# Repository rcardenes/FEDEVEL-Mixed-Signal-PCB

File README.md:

Mixed-Signal Demo PCB
=====================

Demo board project for the "Mixed-Signal Hardware Design with KiCAD" course, by
Phil Salmony (of Phil's Lab fame) at [FEDEVEL](fedevel.com). 

The project was created from scratch using KiCAD 8.0, following the course lectures.
It comes with all the relevant files, including missing footprints and 3D models.
Several of the 3D models were downloaded, and are not to be used without permission:

- HRO_TYPE-C-31-M-12.step (USB receptacle, from GrabCad.com)
- 31-5640-1010.stp (BNC connectors, from Amphenol.com)
- L_Coilcraft_XxL4020.step (for the matching inductor, from 3DContentCentral.com)

The models for the CMF3216 common-mode choke, and the RGB LED (E6C...) were created
by myself in FreeCAD and are free to use, with appropriate acknowledgment.

The project includes Gerber files, and BOM/Placement files. All relevant parts include
an MNP field with JCLPCB/LCSC part numbers, and the assembly files were generated using
the "Fabrication Toolkit" plugin, which generates JLCPCB-compatible output.

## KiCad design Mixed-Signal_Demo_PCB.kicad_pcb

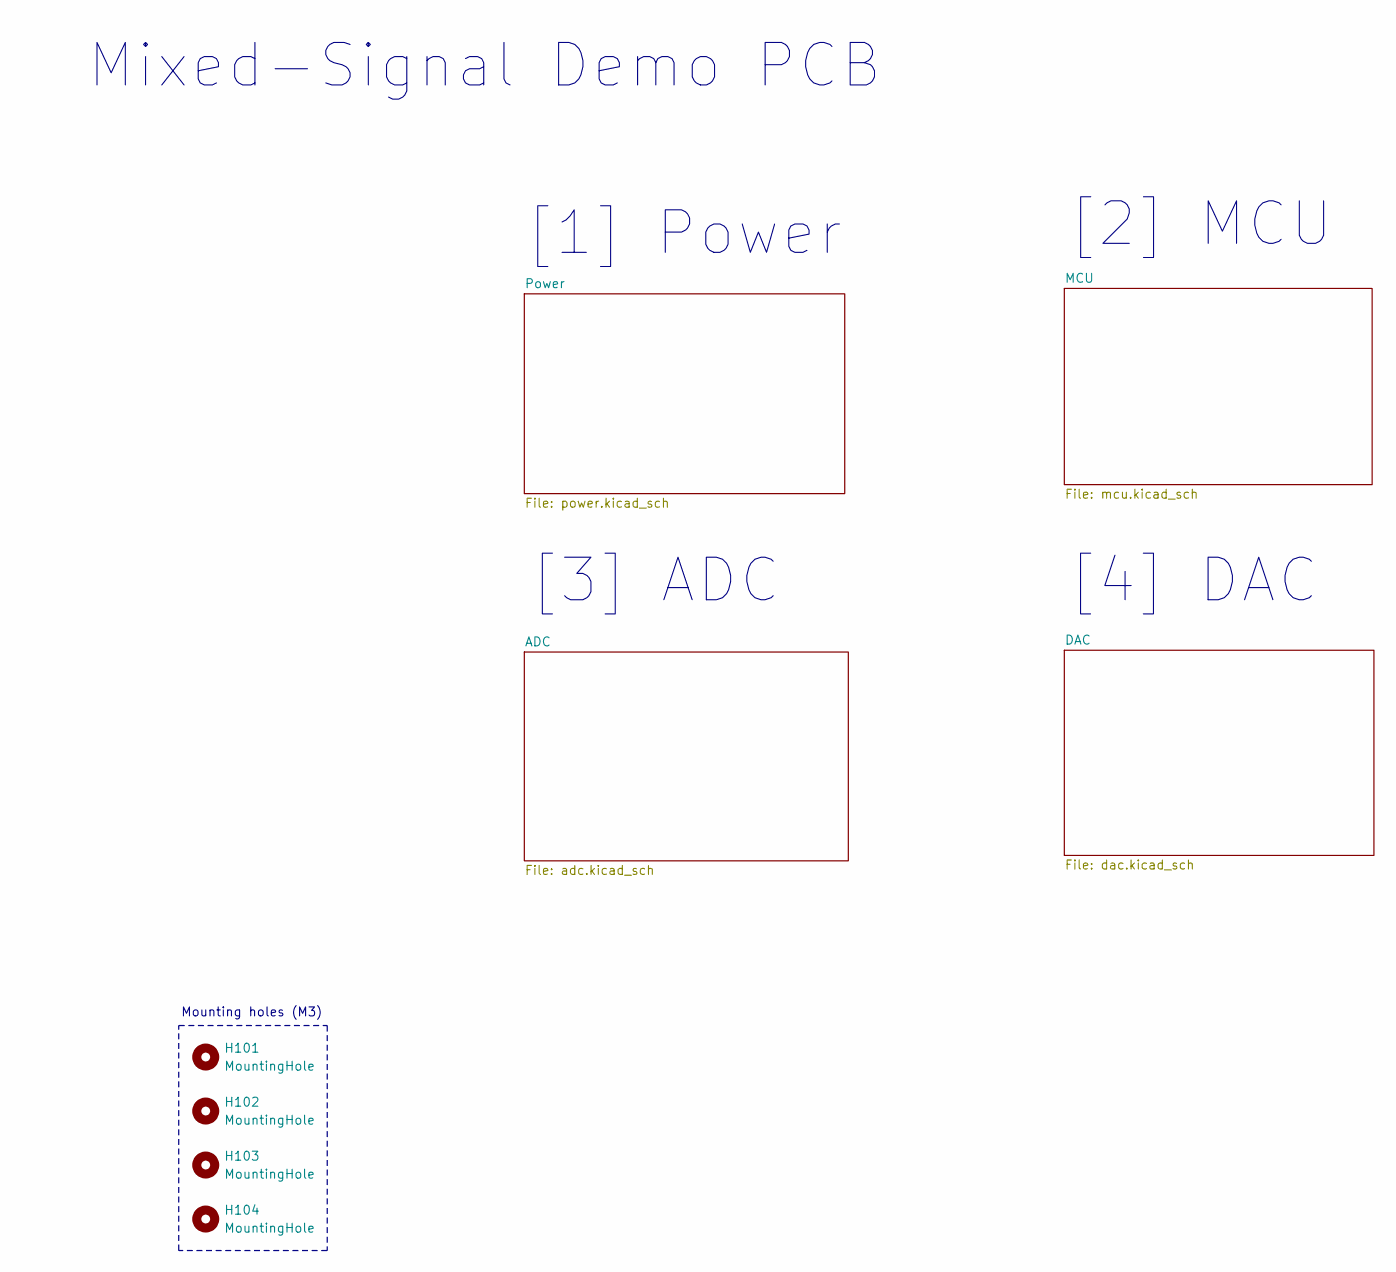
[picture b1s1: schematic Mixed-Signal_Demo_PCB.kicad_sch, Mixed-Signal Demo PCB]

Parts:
H101, H102, H103, H104: MountingHole; MountingHole_3.2mm_M3

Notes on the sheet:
[2] MCU
[1] Power
[3] ADC
[4] DAC
Mounting holes (M3)
Mixed-Signal Demo PCB

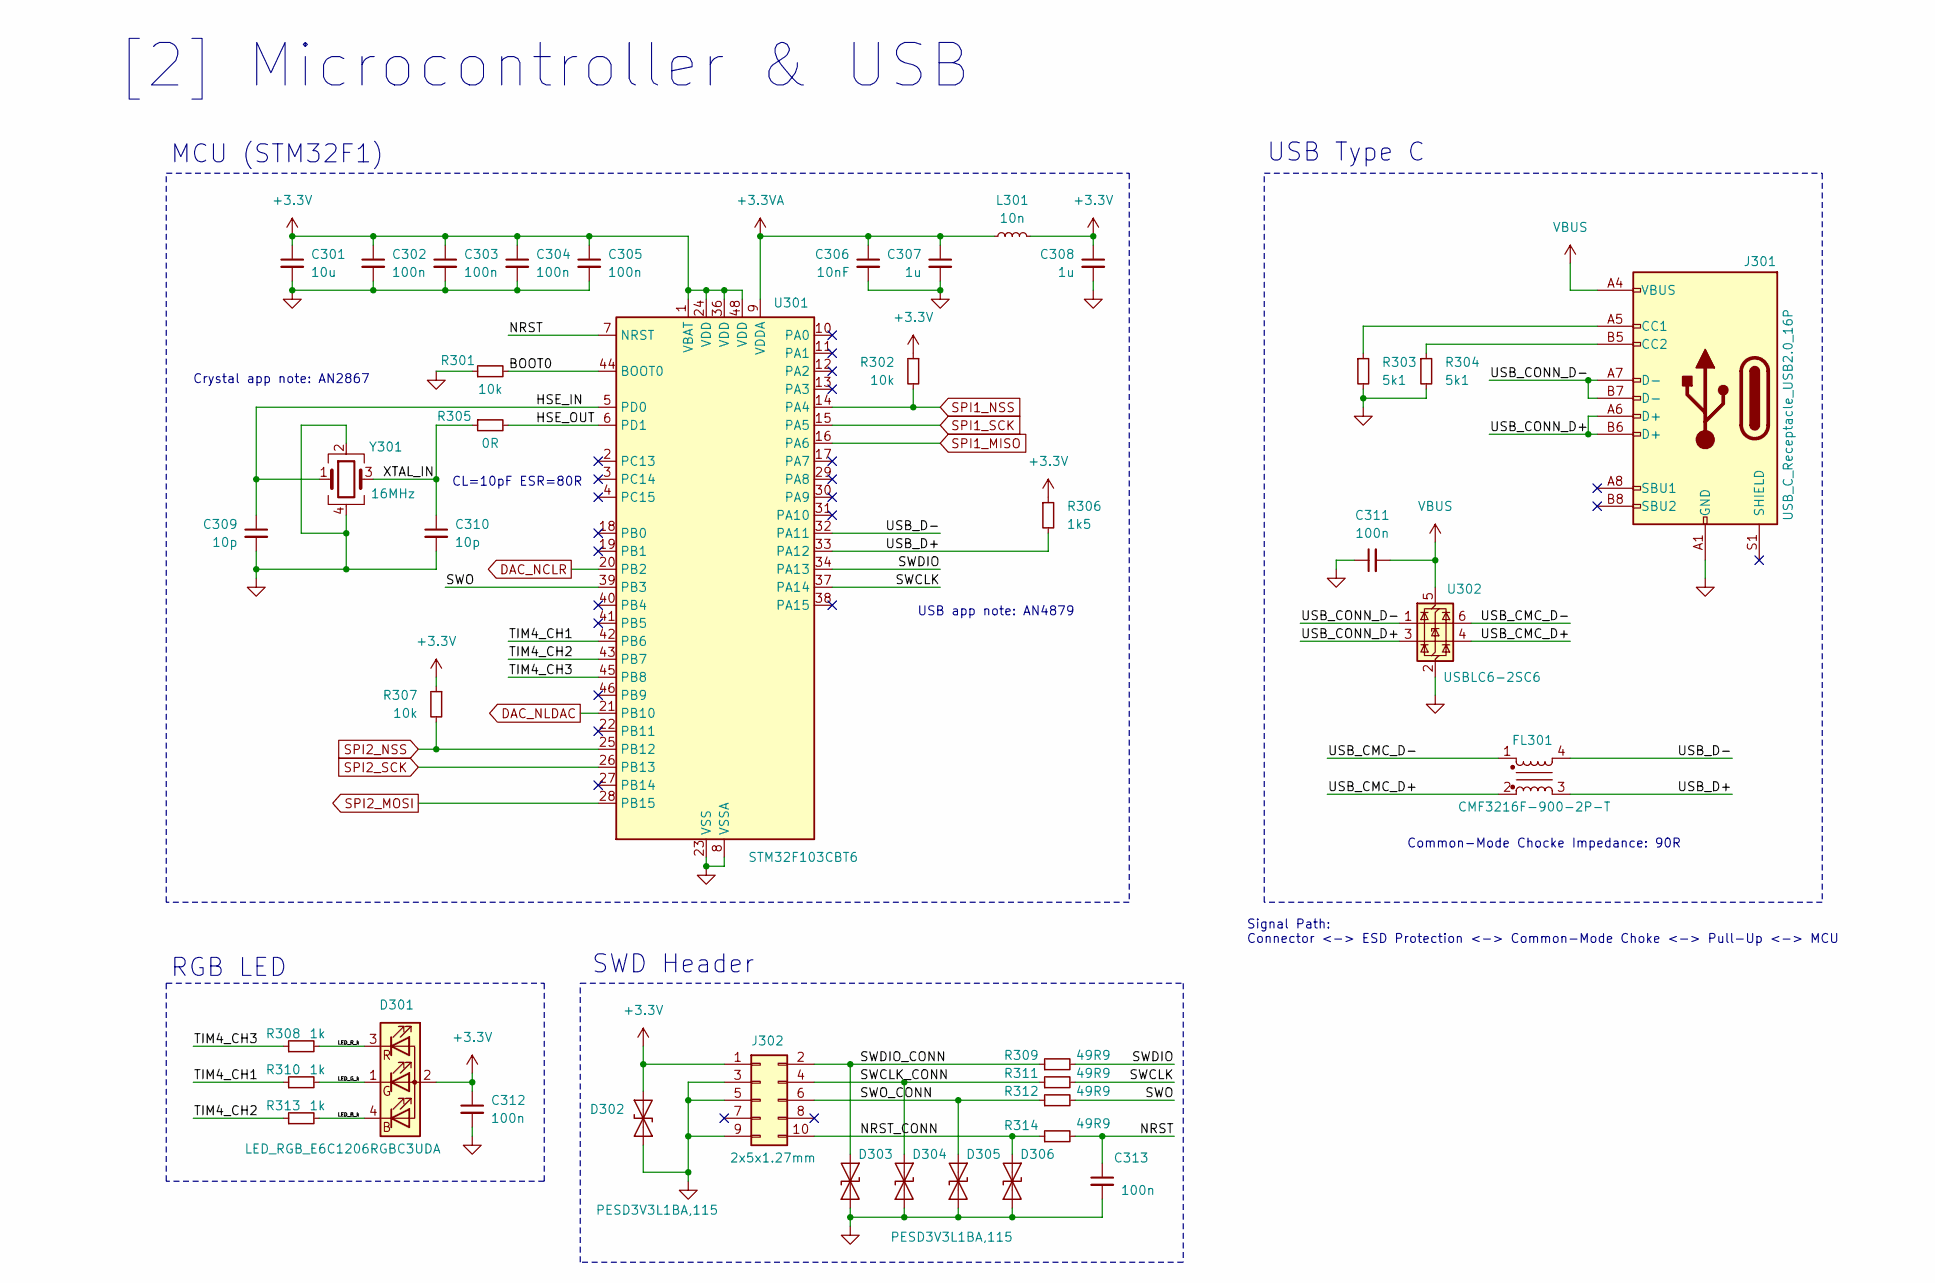
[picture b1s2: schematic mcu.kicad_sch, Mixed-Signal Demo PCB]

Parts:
C301: 10u; C_0603_1608Metric; MPN C19702
C302, C303, C304, C305, C311, C312, C313: 100n; C_0402_1005Metric; MPN C1525
C306: 10nF; C_0402_1005Metric; MPN C15195
C307, C308: 1u; C_0603_1608Metric; MPN C15849
C309, C310: 10p; C_0402_1005Metric; MPN C32949
D301: LED_RGB_E6C1206RGBC3UDA; E6C1206RGBC3UDA; MPN C375571
D302, D303, D304, D305, D306: PESD3V3L1BA,115; D_SOD-323; MPN C51450
FL301: CMF3216F-900-2P-T; CMF3216F; MPN C963740
J301: USB_C_Receptacle_USB2.0_16P; USB_C_Receptacle_HRO_TYPE-C-31-M-12; MPN C319148
J302: 2x5x1.27mm; PinHeader_2x05_P1.27mm_Vertical_SMD; MPN C920813
L301: 10n; L_0402_1005Metric; MPN C404632
R301, R302, R307: 10k; R_0402_1005Metric; MPN C25744
R303, R304: 5k1; R_0402_1005Metric; MPN C25905
R305: 0R; R_0402_1005Metric; MPN C17168
R306: 1k5; R_0402_1005Metric; MPN C25867
R308, R310, R313: 1k; R_0402_1005Metric; MPN C11702
R309, R311, R312, R314: 49R9; R_0402_1005Metric; MPN C25120
U301: STM32F103CBT6; LQFP-48_7x7mm_P0.5mm; MPN C8304
U302: USBLC6-2SC6; SOT-23-6; MPN USBLC6-2SC6
Y301: 16MHz; Crystal_SMD_3225-4Pin_3.2x2.5mm; MPN C362342

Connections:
+3.3V: C301.1, C302.1, C303.1, C304.1, C305.1, C308.1, C312.1, D301.2 (A), D302.2 (A2), J302.1, L301.2, R302.1, R306.1, R307.1, U301.1 (VBAT), U301.24 (VDD), U301.36 (VDD), U301.48 (VDD); also elsewhere on the board
+3.3VA: C306.1, C307.1, L301.1, U301.9 (VDDA); also elsewhere on the board
/MCU/BOOT0: R301.2, U301.44 (BOOT0)
/MCU/HSE_IN: C309.1, U301.5 (PD0), Y301.1
/MCU/HSE_OUT: R305.2, U301.6 (PD1)
/MCU/LED_B_k: D301.4 (BK), R313.2
/MCU/LED_G_k: D301.1 (GK), R310.2
/MCU/LED_R_k: D301.3 (RK), R308.2
/MCU/NRST: C313.1, R314.2, U301.7 (NRST)
/MCU/NRST_CONN: D306.2 (A2), J302.10, R314.1
/MCU/SWCLK: R311.2, U301.37 (PA14)
/MCU/SWCLK_CONN: D304.2 (A2), J302.4, R311.1
/MCU/SWDIO: R309.2, U301.34 (PA13)
/MCU/SWDIO_CONN: D303.2 (A2), J302.2, R309.1
/MCU/SWO: R312.2, U301.39 (PB3)
/MCU/SWO_CONN: D305.2 (A2), J302.6, R312.1
/MCU/TIM4_CH1: R310.1, U301.42 (PB6)
/MCU/TIM4_CH2: R313.1, U301.43 (PB7)
/MCU/TIM4_CH3: R308.1, U301.45 (PB8)
/MCU/USB_CMC_D+: FL301.2, U302.4 (I/O2)
/MCU/USB_CMC_D-: FL301.1, U302.6 (I/O1)
/MCU/USB_CONN_D+: J301.A6 (D+), J301.B6 (D+), U302.3 (I/O2)
/MCU/USB_CONN_D-: J301.A7 (D-), J301.B7 (D-), U302.1 (I/O1)
/MCU/USB_D+: FL301.3, R306.2, U301.33 (PA12)
/MCU/USB_D-: FL301.4, U301.32 (PA11)
/MCU/XTAL_IN: C310.1, R305.1, Y301.3
DAC_NCLR: U301.20 (PB2); also elsewhere on the board
DAC_NLDAC: U301.21 (PB10); also elsewhere on the board
GND: C301.2, C302.2, C303.2, C304.2, C305.2, C306.2, C307.2, C308.2, C309.2, C310.2, C311.1, C312.2, C313.2, D302.1 (A1), D303.1 (A1), D304.1 (A1), D305.1 (A1), D306.1 (A1), J301.A1 (GND), J301.A12 (GND), J301.B1 (GND), J301.B12 (GND), J302.3, J302.5, J302.9, R301.1, R303.2, R304.2, U301.8 (VSSA), U301.23 (VSS), U301.35 (VSS), U301.47 (VSS), U302.2 (GND), Y301.2, Y301.4; also elsewhere on the board
unnamed: J301.A5 (CC1), R303.1
unnamed: J301.B5 (CC2), R304.1
SPI1_MISO: U301.16 (PA6); also elsewhere on the board
SPI1_NSS: R302.2, U301.14 (PA4); also elsewhere on the board
SPI1_SCK: U301.15 (PA5); also elsewhere on the board
SPI2_MOSI: U301.28 (PB15); also elsewhere on the board
SPI2_NSS: R307.2, U301.25 (PB12); also elsewhere on the board
SPI2_SCK: U301.26 (PB13); also elsewhere on the board
VBUS: C311.2, J301.A4 (VBUS), J301.A9 (VBUS), J301.B4 (VBUS), J301.B9 (VBUS), U302.5 (VBUS); also elsewhere on the board

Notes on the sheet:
MCU (STM32F1)
[2] Microcontroller & USB
RGB LED
SWD Header
Crystal app note: AN2867
CL=10pF ESR=80R
Signal Path: Connector <-> ESD Protection <-> Common-Mode Choke <-> Pull-Up <-> MCU
USB app note: AN4879
Common-Mode Chocke Impedance: 90R
USB Type C

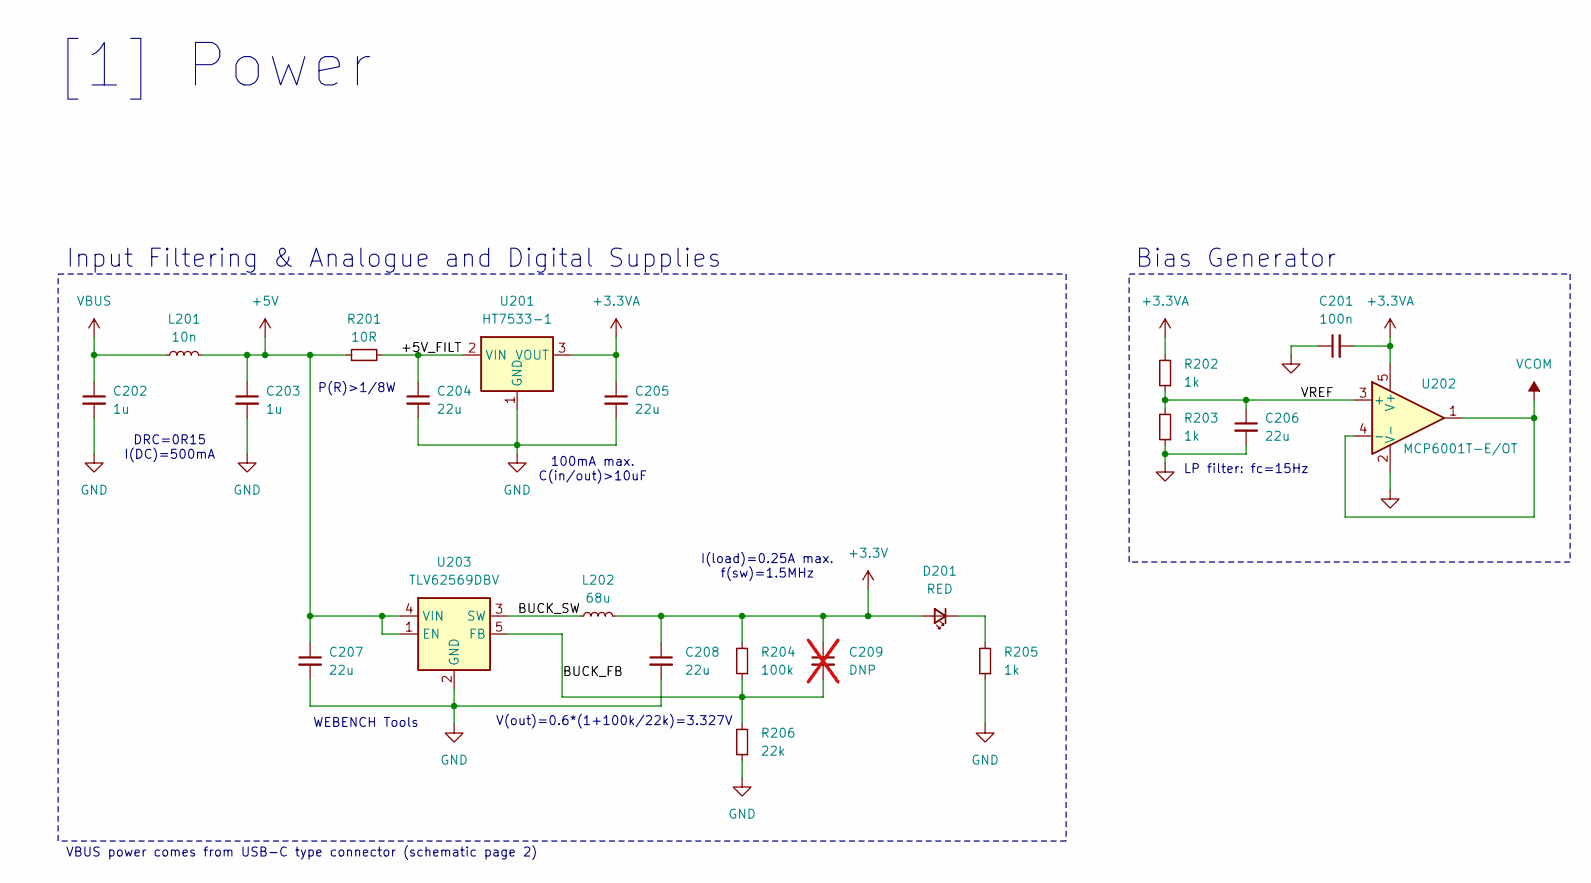
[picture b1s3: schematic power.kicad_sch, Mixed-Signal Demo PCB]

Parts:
C201: 100n; C_0402_1005Metric; MPN C1525
C202, C203: 1u; C_0603_1608Metric; MPN C15849
C204, C205, C206, C207, C208: 22u; C_0805_2012Metric; MPN C45783
C209: DNP; C_0402_1005Metric; not fitted
D201: RED; LED_0603_1608Metric; MPN C2286
L201: 10n; L_0402_1005Metric; MPN C404632
L202: 68u; L_Coilcraft_XxL4020; MPN C3151182
R201: 10R; R_0805_2012Metric; MPN C17415
R202, R203, R205: 1k; R_0402_1005Metric; MPN C11702
R204: 100k; R_0402_1005Metric; MPN 0402
R206: 22k; R_0402_1005Metric; MPN C25768
U201: HT7533-1; SOT-89-3; MPN C14289
U202: MCP6001T-E/OT; SOT-23-5; MPN C29429
U203: TLV62569DBV; SOT-23-5; MPN C2864104

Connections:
+3.3V: C208.1, C209.1, D201.2 (A), L202.2, R204.2; also elsewhere on the board
+3.3VA: C201.2, C205.1, R202.2, U201.3 (VOUT), U202.5 (V+); also elsewhere on the board
+5V: C203.1, C207.1, L201.2, R201.1, U203.1 (EN), U203.4 (VIN); also elsewhere on the board
/Power/+5V_FILT: C204.1, R201.2, U201.2 (VIN)
/Power/BUCK_FB: C209.2, R204.1, R206.2, U203.5 (FB)
/Power/BUCK_SW: L202.1, U203.3 (SW)
/Power/VREF: C206.1, R202.1, R203.2, U202.3 (+)
GND: C201.1, C202.2, C203.2, C204.2, C205.2, C206.2, C207.2, C208.2, R203.1, R205.1, R206.1, U201.1 (GND), U202.2 (V-), U203.2 (GND); also elsewhere on the board
unnamed: D201.1 (K), R205.2
VBUS: C202.1, L201.1; also elsewhere on the board
VCOM: U202.1, U202.4 (-); also elsewhere on the board

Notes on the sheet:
100mA max. C(in/out)>10uF
I(load)=0.25A max. f(sw)=1.5MHz
Bias Generator
DRC=0R15 I(DC)=500mA
P(R)>1/8W
LP filter: fc=15Hz
V(out)=0.6*(1+100k/22k)=3.327V
VBUS power comes from USB-C type connector (schematic page 2)
[1] Power
WEBENCH Tools
Input Filtering & Analogue and Digital Supplies

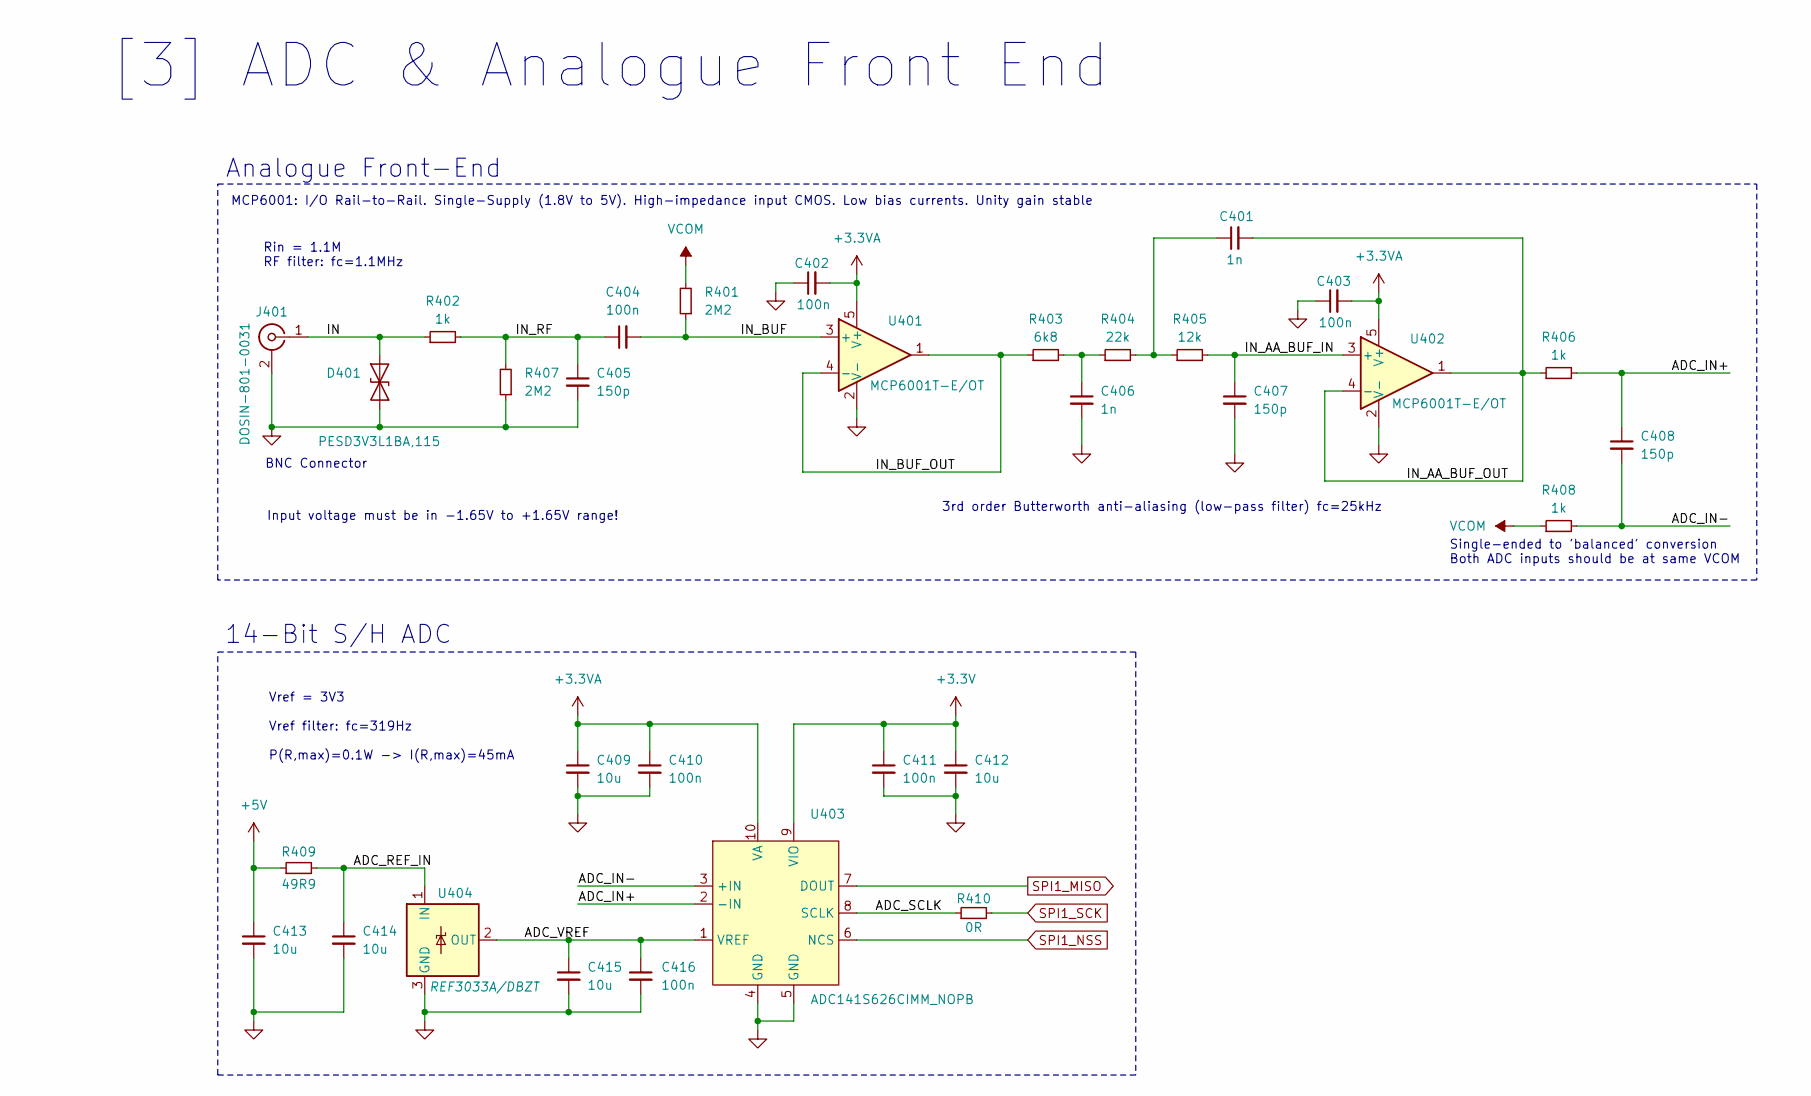
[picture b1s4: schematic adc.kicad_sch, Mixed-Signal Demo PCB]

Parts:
C401, C406: 1n; C_0402_1005Metric; MPN C1523
C402, C403, C404, C410, C411, C416: 100n; C_0402_1005Metric; MPN C1525
C405, C407, C408: 150p; C_0402_1005Metric; MPN C106998
C409, C412, C413, C414, C415: 10u; C_0603_1608Metric; MPN C19702
D401: PESD3V3L1BA,115; D_SOD-323; MPN C51450
J401: DOSIN-801-0031; BNC_Amphenol_B6252HB-NPP3G-50_Horizontal; MPN C521205
R401, R407: 2M2; R_0402_1005Metric; MPN C274901
R402, R406, R408: 1k; R_0402_1005Metric; MPN C11702
R403: 6k8; R_0603_1608Metric; MPN C23212
R404: 22k; R_0402_1005Metric; MPN C25768
R405: 12k; R_0402_1005Metric; MPN C25752
R409: 49R9; R_0402_1005Metric; MPN C25120
R410: 0R; R_0402_1005Metric; MPN C17168
U401, U402: MCP6001T-E/OT; SOT-23-5; MPN C29429
U403: ADC141S626CIMM_NOPB; VSSOP-10_3x3mm_P0.5mm; MPN C206494
U404: REF3033A/DBZT; SOT-23; MPN C2872391

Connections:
+3.3V: C411.1, C412.1, U403.9 (VIO); also elsewhere on the board
+3.3VA: C402.2, C403.2, C409.1, C410.1, U401.5 (V+), U402.5 (V+), U403.10 (VA); also elsewhere on the board
+5V: C413.1, R409.1; also elsewhere on the board
/ADC/ADC_IN+: C408.1, R406.2, U403.2 (-IN)
/ADC/ADC_IN-: C408.2, R408.2, U403.3 (+IN)
/ADC/ADC_REF_IN: C414.1, R409.2, U404.1 (IN)
/ADC/ADC_SCLK: R410.1, U403.8 (SCLK)
/ADC/ADC_VREF: C415.1, C416.1, U403.1 (VREF), U404.2 (OUT)
/ADC/IN: D401.2 (A2), J401.1 (In), R402.1
/ADC/IN_AA_BUF_IN: C407.1, R405.2, U402.3 (+)
/ADC/IN_AA_BUF_OUT: C401.2, R406.1, U402.1, U402.4 (-)
/ADC/IN_BUF: C404.2, R401.1, U401.3 (+)
/ADC/IN_BUF_OUT: R403.1, U401.1, U401.4 (-)
/ADC/IN_RF: C404.1, C405.1, R402.2, R407.2
GND: C402.1, C403.1, C405.2, C406.2, C407.2, C409.2, C410.2, C411.2, C412.2, C413.2, C414.2, C415.2, C416.2, D401.1 (A1), J401.2 (Ext), R407.1, U401.2 (V-), U402.2 (V-), U403.4 (GND), U403.5 (GND), U404.3 (GND); also elsewhere on the board
unnamed: C401.1, R404.2, R405.1
unnamed: C406.1, R403.2, R404.1
SPI1_MISO: U403.7 (DOUT); also elsewhere on the board
SPI1_NSS: U403.6 (NCS); also elsewhere on the board
SPI1_SCK: R410.2; also elsewhere on the board
VCOM: R401.2, R408.1; also elsewhere on the board

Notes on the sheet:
[3] ADC & Analogue Front End
MCP6001: I/O Rail-to-Rail. Single-Supply (1.8V to 5V). High-impedance input CMOS. Low bias currents. Unity gain stable
Input voltage must be in -1.65V to +1.65V range!
Analogue Front-End
3rd order Butterworth anti-aliasing (low-pass filter) fc=25kHz
Single-ended to 'balanced' conversion Both ADC inputs should be at same VCOM
Rin = 1.1M RF filter: fc=1.1MHz
BNC Connector
14-Bit S/H ADC
Vref = 3V3 Vref filter: fc=319Hz P(R,max)=0.1W -> I(R,max)=45mA

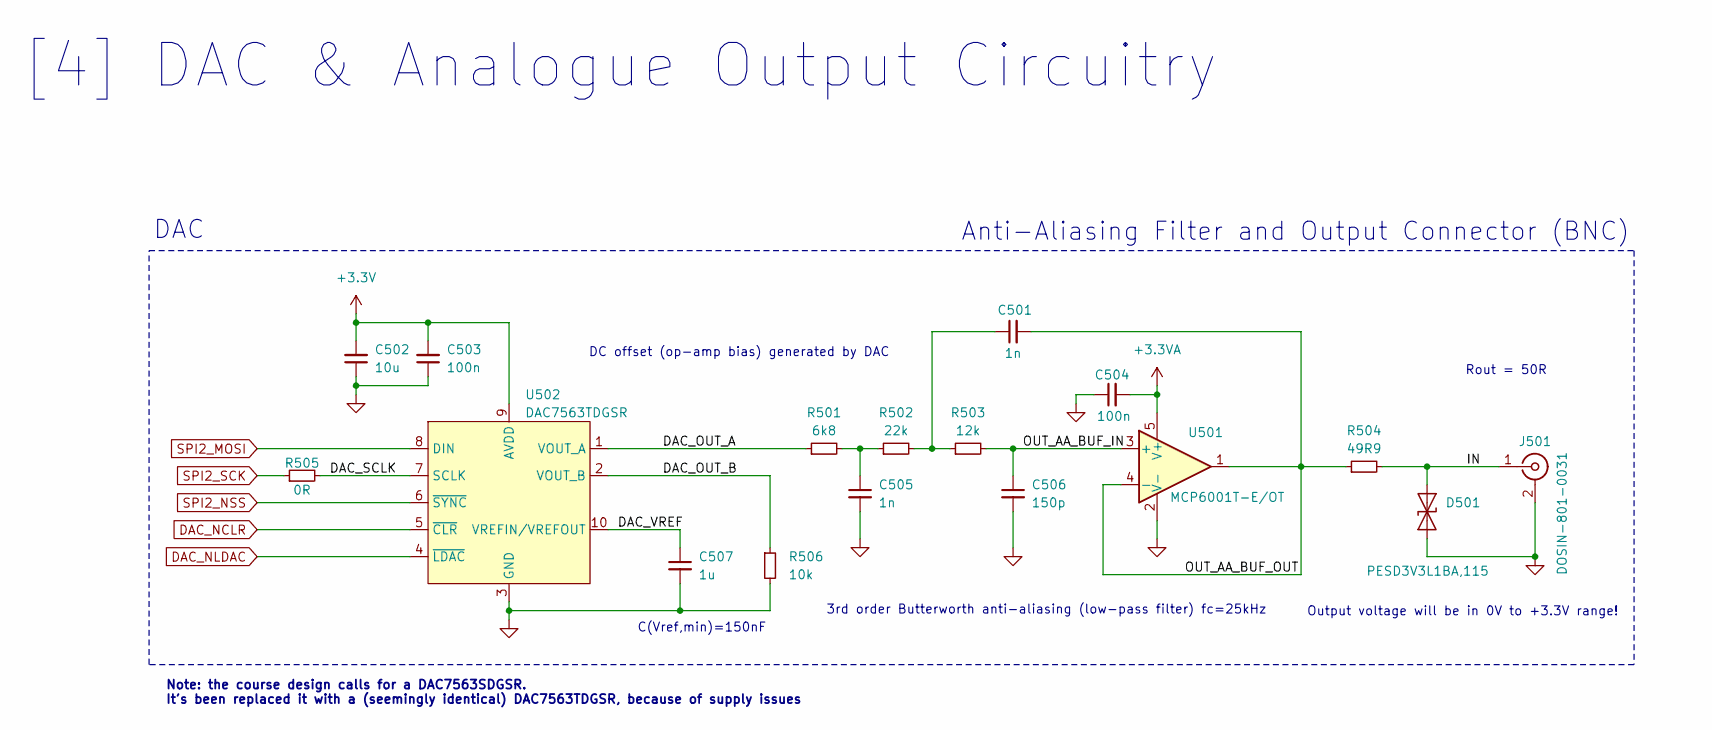
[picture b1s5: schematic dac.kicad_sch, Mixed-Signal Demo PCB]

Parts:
C501, C505: 1n; C_0402_1005Metric; MPN C1523
C502: 10u; C_0603_1608Metric; MPN C19702
C503, C504: 100n; C_0402_1005Metric; MPN C1525
C506: 150p; C_0402_1005Metric; MPN C106998
C507: 1u; C_0603_1608Metric; MPN C15849
D501: PESD3V3L1BA,115; D_SOD-323; MPN C51450
J501: DOSIN-801-0031; BNC_Amphenol_B6252HB-NPP3G-50_Horizontal; MPN C521205
R501: 6k8; R_0603_1608Metric; MPN C23212
R502: 22k; R_0402_1005Metric; MPN C25768
R503: 12k; R_0402_1005Metric; MPN C25752
R504: 49R9; R_0402_1005Metric; MPN C25120
R505: 0R; R_0402_1005Metric; MPN C17168
R506: 10k; R_0402_1005Metric; MPN C25744
U501: MCP6001T-E/OT; SOT-23-5; MPN C29429
U502: DAC7563TDGSR; VSSOP-10_3x3mm_P0.5mm; MPN C2879196

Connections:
+3.3V: C502.2, C503.2, U502.9 (AVDD); also elsewhere on the board
+3.3VA: C504.2, U501.5 (V+); also elsewhere on the board
/DAC/DAC_OUT_A: R501.1, U502.1 (VOUT_A)
/DAC/DAC_OUT_B: R506.1, U502.2 (VOUT_B)
/DAC/DAC_SCLK: R505.2, U502.7 (SCLK)
/DAC/DAC_VREF: C507.1, U502.10 (VREFIN/VREFOUT)
/DAC/IN: D501.2 (A2), J501.1 (In), R504.2
/DAC/OUT_AA_BUF_IN: C506.1, R503.2, U501.3 (+)
/DAC/OUT_AA_BUF_OUT: C501.2, R504.1, U501.1, U501.4 (-)
DAC_NCLR: U502.5 (~CLR); also elsewhere on the board
DAC_NLDAC: U502.4 (~LDAC); also elsewhere on the board
GND: C502.1, C503.1, C504.1, C505.2, C506.2, C507.2, D501.1 (A1), J501.2 (Ext), R506.2, U501.2 (V-), U502.3 (GND); also elsewhere on the board
unnamed: C501.1, R502.2, R503.1
unnamed: C505.1, R501.2, R502.1
SPI2_MOSI: U502.8 (DIN); also elsewhere on the board
SPI2_NSS: U502.6 (~SYNC); also elsewhere on the board
SPI2_SCK: R505.1; also elsewhere on the board

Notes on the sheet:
C(Vref,min)=150nF
3rd order Butterworth anti-aliasing (low-pass filter) fc=25kHz
[4] DAC & Analogue Output Circuitry
Anti-Aliasing Filter and Output Connector (BNC)
Note: the course design calls for a DAC7563SDGSR. It's been replaced it with a (seemingly identical) DAC7563TDGSR, because of supply issues
Rout = 50R
DAC
Output voltage will be in 0V to +3.3V range!
DC offset (op-amp bias) generated by DAC

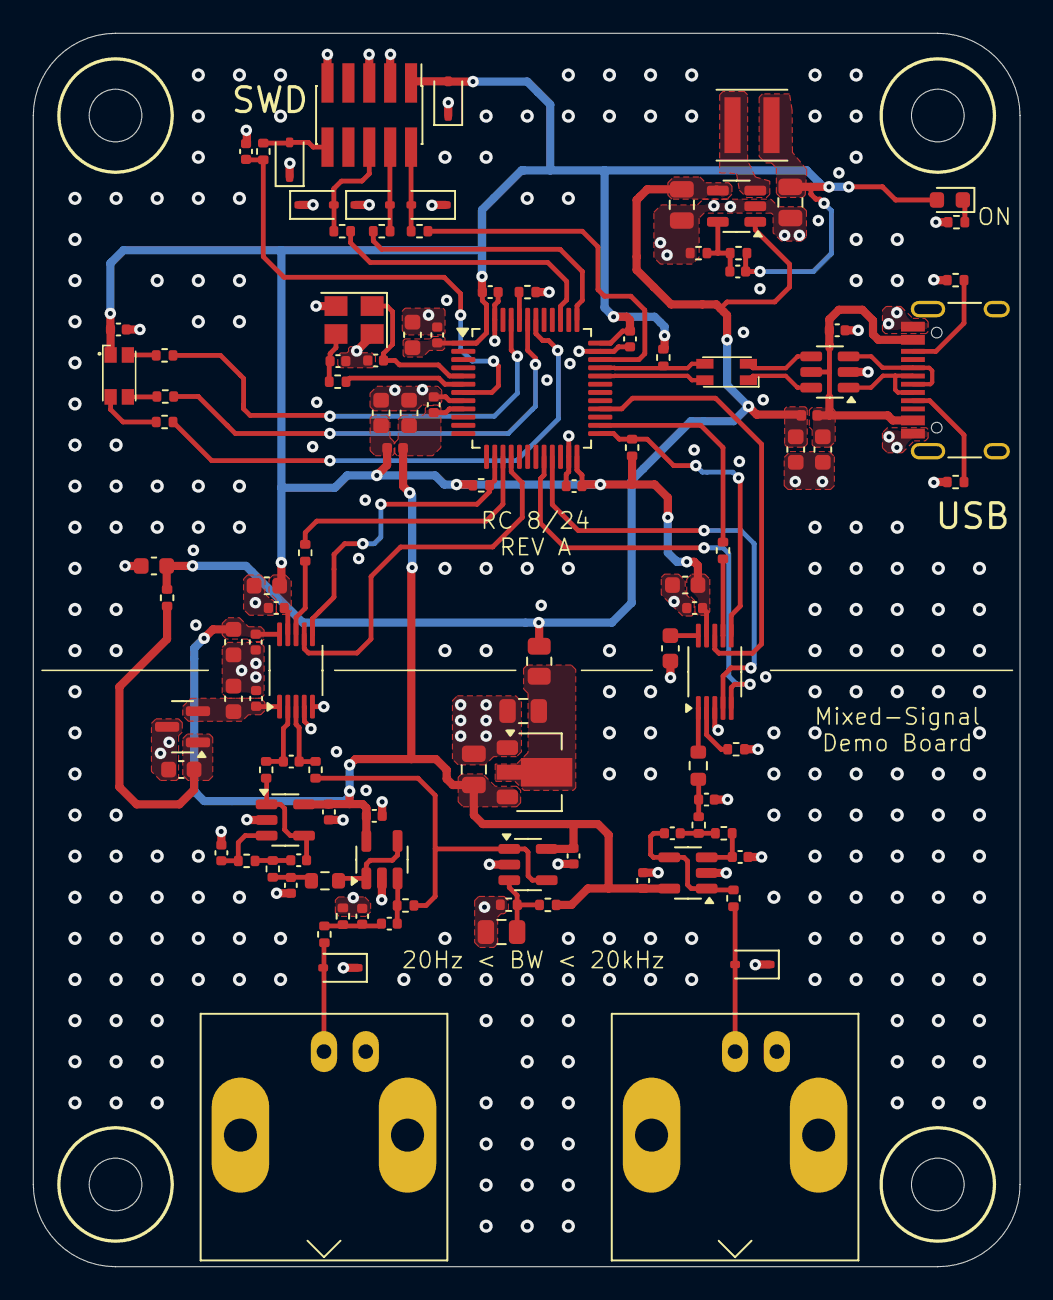
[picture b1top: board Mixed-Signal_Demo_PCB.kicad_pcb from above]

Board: 4 copper layers, 60.0 x 75.0 mm, 114 parts (0 on the bottom side), 67 nets.

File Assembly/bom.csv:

Designator,Footprint,Quantity,Value,LCSC Part #
"C201, C302, C303, C304, C305, C311, C312, C313, C402, C403, C404, C410, C411, C416, C503, C504",0402,16,100n,C1525
"C202, C203, C307, C308, C507",0603,5,1u,C15849
"C204, C205, C206, C207, C208",0805,5,22u,C45783
C209,0402,1,DNP,
"C301, C409, C412, C413, C414, C415, C502",0603,7,10u,C19702
C306,0402,1,10nF,C15195
"C309, C310",0402,2,10p,C32949
"C401, C406, C501, C505",0402,4,1n,C1523
"C405, C407, C408, C506",0402,4,150p,C106998
D201,0603,1,RED,C2286
D301,E6C1206RGBC3UDA,1,LED_RGB_E6C1206RGBC3UDA,C375571
"D302, D303, D304, D305, D306, D401, D501",D_SOD-323,7,"PESD3V3L1BA,115",C51450
FL301,CMF3216F,1,CMF3216F-900-2P-T,C963740
J301,USB_C_Receptacle_HRO_TYPE-C-31-M-12,1,USB_C_Receptacle_USB2.0_16P,C319148
J302,PinHeader_2x05_P1.27mm_Vertical_SMD,1,2x5x1.27mm,C920813
"J401, J501",BNC_Amphenol_B6252HB-NPP3G-50_Horizontal,2,DOSIN-801-0031,C521205
"L201, L301",0402,2,10n,C404632
L202,L_Coilcraft_XxL4020,1,68u,C3151182
R201,0805,1,10R,C17415
"R202, R203, R205, R308, R310, R313, R402, R406, R408",0402,9,1k,C11702
R204,0402,1,100k,0402
"R206, R404, R502",0402,3,22k,C25768
"R301, R302, R307, R506",0402,4,10k,C25744
"R303, R304",0402,2,5k1,C25905
"R305, R410, R505",0402,3,0R,C17168
R306,0402,1,1k5,C25867
"R309, R311, R312, R314, R409, R504",0402,6,49R9,C25120
"R401, R407",0402,2,2M2,C274901
"R403, R501",0603,2,6k8,C23212
"R405, R503",0402,2,12k,C25752
U201,SOT-89-3,1,HT7533-1,C14289
"U202, U401, U402, U501",SOT-23-5,4,MCP6001T-E/OT, C29429
U203,SOT-23-5,1,TLV62569DBV,C2864104
U301,LQFP-48_7x7mm_P0.5mm,1,STM32F103CBT6,C8304
U302,SOT-23-6,1,USBLC6-2SC6,USBLC6-2SC6
U403,VSSOP-10_3x3mm_P0.5mm,1,ADC141S626CIMM_NOPB,C206494
U404,SOT-23,1,REF3033A/DBZT,C2872391
U502,VSSOP-10_3x3mm_P0.5mm,1,DAC7563TDGSR,C2879196
Y301,Crystal_SMD_3225-4Pin_3.2x2.5mm,1,16MHz,C362342

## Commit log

2024-07-31 Lesson 5: top level schematic + power module
2024-07-31 Reannotate based on sheet page number
2024-07-31 Lesson 6: MCU and USB module
2024-07-31 Lesson 7: ADC, DAC, and frontends
2024-07-31 Remove bak files from the git repo
2024-08-01 Lesson 8: Reannotation, running ERC for schematic
2024-08-01 Lesson 8: Assigned most footprints. Added missing ones
2024-08-02 Lesson 11: Adjusted capacitor footprints and set up PCB defaults
2024-08-02 Lesson 12: MCU and USB rough placement
2024-08-02 Lesson 12: ADC and DAC
2024-08-03 Lesson 12: Rest of placement, some rearrangements. Added models
2024-08-03 Lesson 13: Routing
2024-08-03 Lesson 14: Finishing touches
2024-08-04 Manufacture: Add part numbers
2024-08-04 Assembly files
2024-08-04 Add README.md
